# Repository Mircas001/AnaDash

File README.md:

# AnaDash - Resource monitor + macropad 
**THIS IS WIP! NOT TESTED YET!**

This is an resource monitor for your PC, also featuring an macropad, inspired by Alex Bailey's system monitor and Hack Club's hackpad program! It allows you to take a quick glance and see your system information, while keeping the screen free for anything you do!
This was made after watching , I've been wanting to make it for 2 years now! I also added an hackpad after seeing the very helpful 

## Features:
- 4x Analog Gauges showing CPU usage, CPU temperature, RAM usage and Swap usage, driven by an MCP4728 chip!
- 8x Cherry MX keys for any macro your heart wishes!
- An LCD display that can show time, notifications and current song!
- An rotary encoder for changing your volume! Including a switch for mute!

## Case
AnaDash consists of embedded-rust-rp2040 parts, each one split into 
- An case, that supports it and holds it, also houses the raspberry, this part is split in two as it's too big to fit in most printers!
 
- An front plate, that you insert heatset inserts into and then screw the parts in, also split in two!
- An front case, which hides all the PCBs and wiring and gives a nice flush finish, split in two as well!
- An encoder, not split in two, with regular rectangular extruding parts for better grip while also keeping printability!

Since the parts are split in two, you'll have to weld them, use an cheap soldering iron or preferentially an plastic welder for this job, since it can damage soldering tips. I can also help you make an version where both parts are one in case you want to print them as one part.

The design files are available [here](https://cad.onshape.com/documents/ea3d35dc7a38396ad80a61d7/w/835ea08936cef2d122cf7568/e/898c0cf3f941f1983e6f2559)

## PCB
This project was designed in KiCad, it uses a pair of 2 layer PCBs, the PCBs were split because the switches had to be at an angle while the pico had to sit straight.
For this to work, you must connect the following, all of the cables are JST-XH, as it features an locking mechanism.
You must make the following connections: (Pinouts are in left to right, when viewed from abovee!, GND will always be the rounded rectangle!) 
- DisplayConnector (BL, SCK, SDA, CS, RESET, CS, VCC, GND) - connect this to the matching pins on the display.
- LeftKeyConnector (Switch1, Switch2, Switch3, Switch4, GND) - The Input Board has matching connections!
- RightKeyConnector (Switch5, Switch6, Switch7, Switch8, GND) - The Input Board has matching connections!
- EncoderConnector (B, A, Switch, GND) - The Input Board has matching connections!

### Main PCB
This Board features the Pico, the DAC, the outputs for the ammeters, the display connector and the connections to the input board.            

[You can check out the PCB and schematic on KiCanvas!](https://kicanvas.org/?repo=https%3A%2F%2Fgithub.com%2FMircas001%2FAnaDash%2Ftree%2Fmain%2Fhardware%2FmainBoard)                                            

### Input PCB
This PCB has all the keys and the encoder and serves to take inputs, it is angled together with the display and gauges at 45 degrees for ergonomics!                 

[You can check out the PCB and schematic on KiCanvas!](https://kicanvas.org/?repo=https%3A%2F%2Fgithub.com%2FMircas001%2FAnaDash%2Ftree%2Fmain%2Fhardware%2FinputBoard)                                         

## Software
The software has been done entirely in rust, it's memory safe, professional, and has great performance!

Before setting up the software, you'll need to install these programs!
- [rustup](https://rustup.rs) - this is the rust toolchain, and it's the recommended way to compile rust code!
- [probe-rs](https://probe.rs) - **ONLY IF** you are gonna upload via an **debug probe**.
- [picotool](https://github.com/raspberrypi/pico-sdk-tools/releases) - **ONLY IF** you are gonna upload via **USB**.
- [lm-sensors](https://github.com/lm-sensors/lm-sensors) - This provides the sensors the driver can read from! Make sure to set it up before!

It's consisted in 3 parts:
- Firmware: Runs the Pico!
- Driver: Gets the info from your PC!
- Shared library: This is so both firmware and hardware agree with each other!

### Firmware
This firmware supports the Raspberry Pi Pico 1!
There are two ways you can upload it to the pico:

#### Upload via debug probe
For this, you need to connect your debug probe to SWD port!
```bash
git clone https://github.com/Mircas001/AnaDash.git
cd AnaDash/software/firmware
cargo run --release
```

#### Upload via USB
For this, all you need to do is connect the Raspberry Pi Pico to your computer via USB, and run with the usb-deploy feature!
```bash
git clone https://github.com/Mircas001/AnaDash.git
cd AnaDash/software/firmware
cargo run -F usb-deploy --release 
```

### Drivers
This only supports Linux for now! But I can answer questions about the code to help anyone who wants to port it! It works as a systemd service that uses udev rules to start as soon as you plug it in!

#### PKGBUILD method
If you run Arch Linux or any other Arch Based distro, you can use this to install! For now you have to manually install the PKGBUILD, but it'll get uploaded to the AUR once it's done!
**This is the recommended method.**
```bash 
git clone https://github.com/Mircas001/anadash-driver.git
cd anadash-driver
makepkg -si
```

#### Compile it yourself
This is more complicated! But it should work!
1. Make sure you are in the dialout group to get serial perms!
```bash
sudo usermod -aG dialout $USER
```
2. Install all the files!
```bash
git clone https://github.com/Mircas001/AnaDash.git
cd AnaDash/software/driver
cargo build --release
sudo cp target/release/anadash-driver /usr/local/bin
sudo chmod 755 /usr/local/bin/anadash-driver 
sudo cp anadash-driver@.service /etc/systemd/system
sudo cp 99-anadash.rules /etc/udev/rules.d
```
3. Reload everything!
```bash 
sudo systemctl daemon-reload
sudo udevadm control --reload-rules
sudo udevadm trigger
```
It should work as soon as you plug in the device!

You're also always welcome to implement these steps in an package file, so other people with your distro have it easier!

### Troubleshooting the drivers
Since it's an systemd service, you can get the logs like this, replacing ```<serialport>``` with the device's serial port! Usually, it's ttyUSB0.
```bash
systemctl status anadash-driver@<serialport>.service
journalctl -u anadash-driver@<serialport>.service
```

## Assembly  
See [assembly.md](https://github.com/Mircas001/AnaDash/blob/main/ASSEMBLY.md)

## Usage
After installation of drivers, assembly, and flashing, the project SHOULD be plug and play. The macropad uses F13-F21, so to setup the macros, just use plug those keys in whatever software you want!  

## Debugging the device
There is an UART port at the main board for debugging!
Also, there are also some key combinations baked in the firmware:
- You can press the 1st key and the 8th key (the two outhermost keys) to reset the pico!
- You can press the 4th key and the 5th key (the two innermost keys) to go into DFU mode!

## Miscellaneous note
You will need to print the labels for the meters in A4 sticker paper, if you are an manufacturer, you should get it custom printed!                           
The labels are available here: [Labels](https://raw.githubusercontent.com/Mircas001/AnaDash/refs/heads/main/production/meterLabels.svg)

There is an LED header added to the PCB, however, I did not implement the code for it, it is there for future use! You are also free to repurpose it!

## BOM
| Designator                                  | Qty |
| ------------------------------------------- | --- |
| 1.77inch ST7735 Display                     | 1   |
| 85C1 Ammeter 5mA                            | 4   |
| FIXME SCREWS                                | 1   |
| M3 X 4.2 X L4.0 Brass Heatset Insert 100pcs | 1   |
| M2 X 3.2 X L4.0 Brass Heatset Insert 100pcs | 1   |
| Countersunk M3x8mm screw                    | 12  |
| Countersunk M3x20mm screw                   | 4   |
| Panhead M2x8mm screw                        | 4   |
| Panhead M3x8mm screw                        | 4   |
| Cherry MX Compatible Switches 10pcs         | 8   |
| XDA2 1U Keycaps 10pcs                       | 1   |
| EC11 Rotary Encoder 20mm with Switch        | 1   |
| JST-XH Kit                                  | 1   |
| Raspberry Pi Pico                           | 1   |
| MCP4728-E                                   | 1   |
| 10uF Tantalum Capacitor 1206                | 1   |
| 100nF Ceramic Capacitor 1206                | 1   |
| 10KΩ 4x0603 Concave Resistor Network        | 1   |
| 665Ω Resistor                               | 4   |
| Main Board at JLCPCB  (PCBA)                | 1   | 
| Input board at JLCPCB                       | 1   |
| 3D Printed parts                            | 7   | 

Details, such as aliexpress links, LCSC part numbers and cost (as of June 2026) are available here: [BOM](https://github.com/Mircas001/AnaDash/blob/main/production/BOM.csv)

It is strongly recommended

You can also get the JLCPCB BOM for the main board (in case you want to get PCBA) here: [BOM](https://github.com/Mircas001/AnaDash/blob/main/production/mainBoard/jlcpcb_bom.csv)

However, if you do get PCBA, it's recommended to only request the soldering of SMD components, as it's cheaper this way! Also, the 665ohm resistors need to be manually filled in, apparently they're so new there's not even a footprint for it! But I believe this issue will go away with time.         

The input board does not feature an JLCPCB BOM for PCBA because they do not have the parts for it! However, I have left the netlist and positions there in case you have an pick and place machine, but official support for assembling it this way is NOT provided! It's recommended to hand solder instead! Only THD components are used there.

## Software used:
This project was designed in:
- [KiCad for the PCBs!](https://www.kicad.org)
- [Visual Studio Code for the software!](https://code.visualstudio.com/)
- [Onshape for the 3D design!](https://onshape.com/)

## TODO List:
- [X] Design the main PCB 
- [X] Design the input PCB
- [X] Design the meters
- [X] Make the drivers
- [X] Make the driver into an actual driver
- [X] Make the firmware
- [ ] Make the Case

## Credits
- [Lex Bailey, for giving me the inspiration to start this project a few years ago, and for help with the meter labels](https://www.youtube.com/watch?v=4J-DTbZlJ5I)
- [Hack Club Macondo program, for the funding](https://macondo.hackclub.com/)
- [OrpheusPad, for serving as reference as to how should the git repo and README look like](https://github.com/qcoral/orpheuspad/tree/main)
- [HackPad program, which, despite not participating in it, guided me through PCB design](https://hackpad.hackclub.com/)
- [CarlKCarlK's clock project which I'm using as inspiration for parts of the codecode](https://github.com/CarlKCarlK/clock)
- [Siliconwit's guide on embassy-usb](https://siliconwit.com/education/embedded-rust-rp2040/usb-device-embassy/)

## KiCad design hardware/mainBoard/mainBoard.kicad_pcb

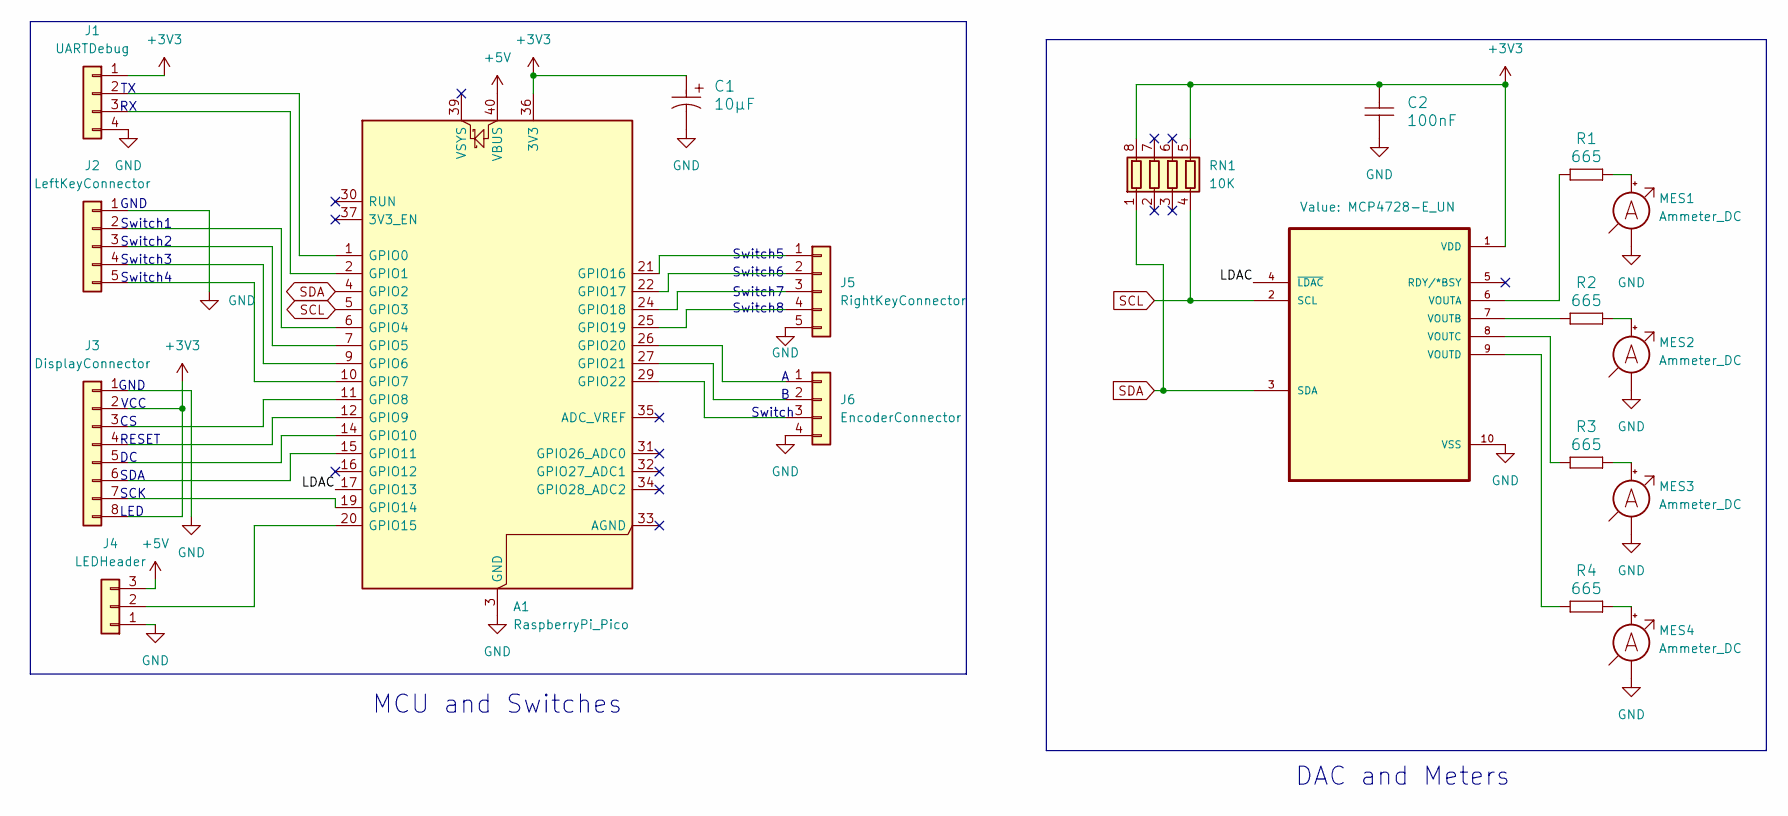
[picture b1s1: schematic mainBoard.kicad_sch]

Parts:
A1: RaspberryPi_Pico; RaspberryPi_Pico_Common_Unspecified; LCSC Part # C42924268
C1: 10µF; CP_EIA-3528-15_AVX-H_HandSolder; LCSC Part # C7171
C2: 100nF; C_1206_3216Metric_Pad1.33x1.80mm_HandSolder; LCSC Part # C24497
J1: UARTDebug; JST_XH_B4B-XH-A_1x04_P2.50mm_Vertical; LCSC Part # C144395
J2: LeftKeyConnector; JST_XH_B5B-XH-A_1x05_P2.50mm_Vertical; LCSC Part # C157991
J3: DisplayConnector; PinHeader_1x08_P2.54mm_Vertical; LCSC Part # C492407
J4: LEDHeader; JST_XH_B3B-XH-A_1x03_P2.50mm_Vertical; LCSC Part # C144394
J5: RightKeyConnector; JST_XH_B5B-XH-A_1x05_P2.50mm_Vertical; LCSC Part # C157991
J6: EncoderConnector; JST_XH_B4B-XH-A_1x04_P2.50mm_Vertical; LCSC Part # C144395
MES1, MES2, MES3, MES4: Ammeter_DC; JST_XH_B2B-XH-A_1x02_P2.50mm_Vertical; LCSC Part # C158012
R1, R2, R3, R4: 665; R_1206_3216Metric_Pad1.30x1.75mm_HandSolder; LCSC Part # C54532953
RN1: 10K; R_Array_Concave_4x0603; LCSC Part # C29718
U1: MCP4728-E_UN; SOP50P490X110-10N; LCSC Part # C108207

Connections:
+3V3: A1.36 (3V3), C1.1, C2.1, J1.1, J3.2, J3.8, RN1.5 (R4.2), RN1.8 (R1.2), U1.1 (VDD)
+5V: A1.40 (VBUS), J4.3
/LDAC: A1.17 (GPIO13), U1.4 (~LDAC)
GND: A1.3 (GND), A1.8 (GND), A1.13 (GND), A1.18 (GND), A1.23 (GND), A1.28 (GND), A1.38 (GND), C1.2, C2.2, J1.4, J2.1, J3.1, J4.1, J5.5, J6.4, MES1.1 (-), MES2.1 (-), MES3.1 (-), MES4.1 (-), U1.10 (VSS)
unnamed: A1.1 (GPIO0), J1.2
unnamed: A1.2 (GPIO1), J1.3
unnamed: A1.6 (GPIO4), J2.2
unnamed: A1.7 (GPIO5), J2.3
unnamed: A1.9 (GPIO6), J2.4
unnamed: A1.10 (GPIO7), J2.5
unnamed: A1.11 (GPIO8), J3.3
unnamed: A1.12 (GPIO9), J3.4
unnamed: A1.14 (GPIO10), J3.5
unnamed: A1.15 (GPIO11), J3.6
unnamed: A1.19 (GPIO14), J3.7
unnamed: A1.20 (GPIO15), J4.2
unnamed: A1.21 (GPIO16), J5.1
unnamed: A1.22 (GPIO17), J5.2
unnamed: A1.24 (GPIO18), J5.3
unnamed: A1.25 (GPIO19), J5.4
unnamed: A1.26 (GPIO20), J6.1
unnamed: A1.27 (GPIO21), J6.2
unnamed: A1.29 (GPIO22), J6.3
unnamed: MES1.2 (+), R1.2
unnamed: MES2.2 (+), R2.2
unnamed: MES3.2 (+), R3.2
unnamed: MES4.2 (+), R4.2
unnamed: R1.1, U1.6 (VOUTA)
unnamed: R2.1, U1.7 (VOUTB)
unnamed: R3.1, U1.8 (VOUTC)
unnamed: R4.1, U1.9 (VOUTD)
SCL: A1.5 (GPIO3), RN1.4 (R4.1), U1.2 (SCL)
SDA: A1.4 (GPIO2), RN1.1 (R1.1), U1.3 (SDA)

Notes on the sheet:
MCU and Switches
GND
Switch2
SCK
Switch
Switch1
DAC and Meters
Switch5
Switch7
GND
Switch6
Switch3
SDA
RESET
Switch8
Switch4
LED
VCC

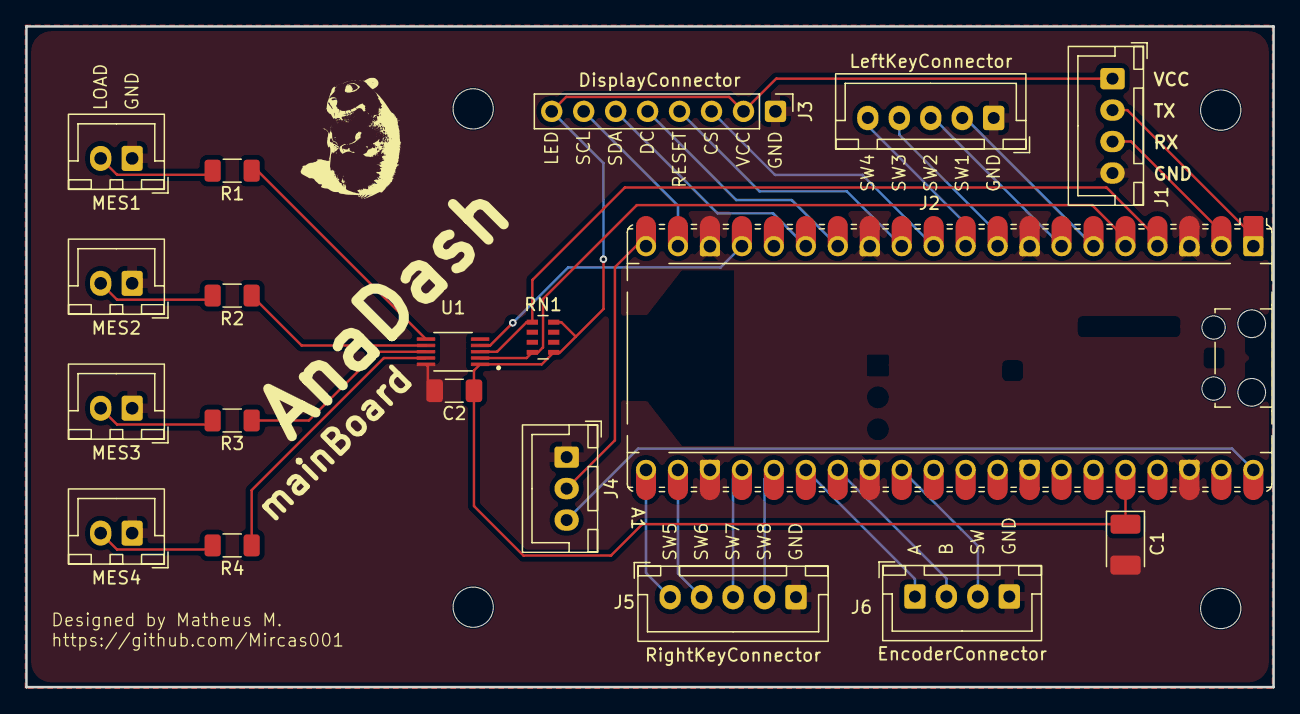
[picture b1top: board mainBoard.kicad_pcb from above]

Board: 2 copper layers, 99.1 x 52.5 mm, 19 parts (0 on the bottom side), 33 nets.

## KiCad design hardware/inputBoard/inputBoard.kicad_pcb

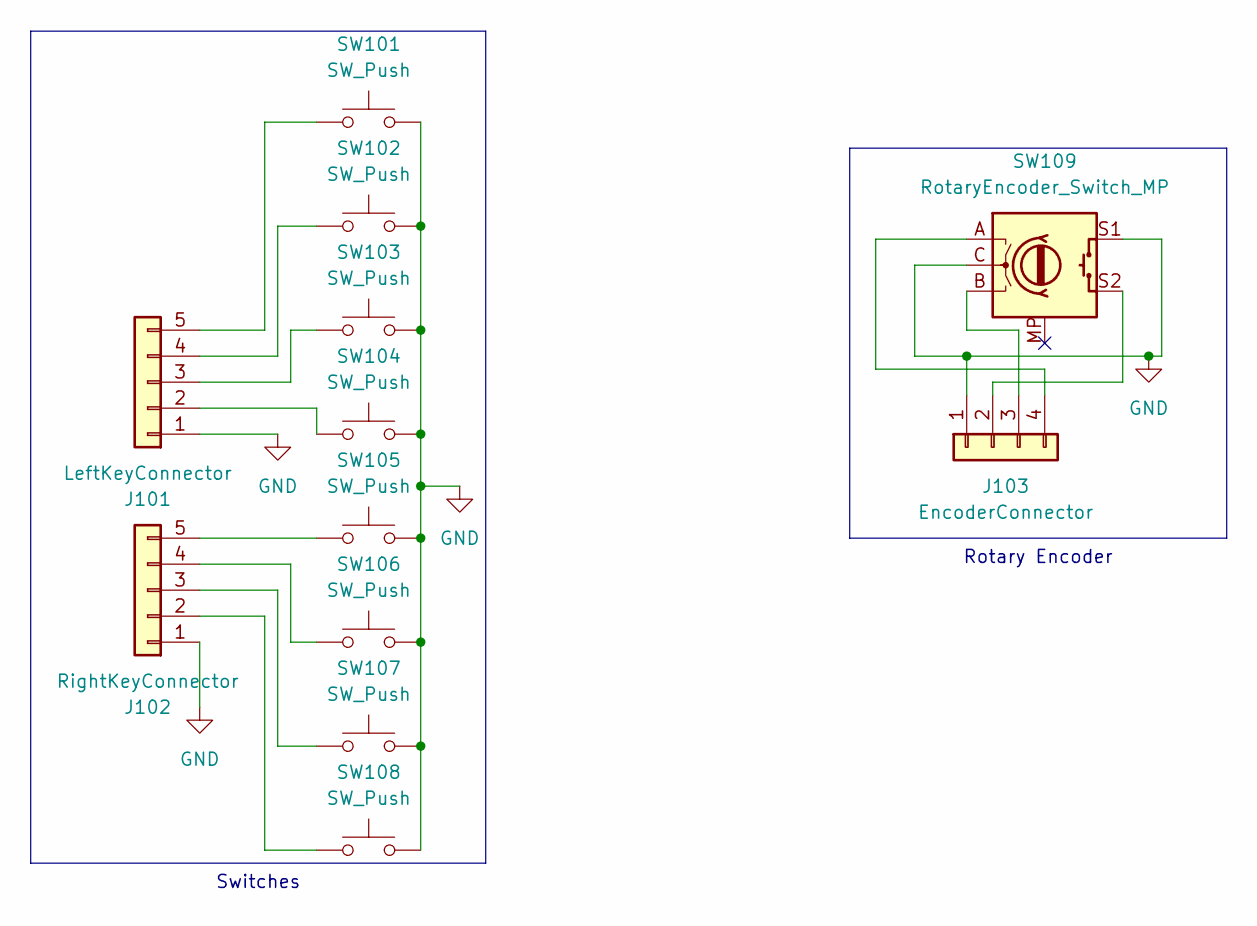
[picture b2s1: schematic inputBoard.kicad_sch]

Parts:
J101: LeftKeyConnector; JST_XH_B5B-XH-A_1x05_P2.50mm_Vertical; LCSC Part # C157991
J102: RightKeyConnector; JST_XH_B5B-XH-A_1x05_P2.50mm_Vertical; LCSC Part # C157991
J103: EncoderConnector; JST_XH_B4B-XH-A_1x04_P2.50mm_Vertical; LCSC Part # C144395
SW101, SW102, SW103, SW104, SW105, SW106, SW107, SW108: SW_Push; SW_Cherry_MX_1.00u_PCB; LCSC Part # N/A
SW109: RotaryEncoder_Switch_MP; RotaryEncoder_Alps_EC11E-Switch_Vertical_H20mm; LCSC Part # C370986

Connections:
GND: J101.1, J102.1, J103.1, SW101.2, SW102.2, SW103.2, SW104.2, SW105.2, SW106.2, SW107.2, SW108.2, SW109.C, SW109.S1
unnamed: J101.2, SW104.1
unnamed: J101.3, SW103.1
unnamed: J101.4, SW102.1
unnamed: J101.5, SW101.1
unnamed: J102.2, SW108.1
unnamed: J102.3, SW107.1
unnamed: J102.4, SW106.1
unnamed: J102.5, SW105.1
unnamed: J103.2, SW109.S2
unnamed: J103.3, SW109.B
unnamed: J103.4, SW109.A

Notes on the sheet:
Switches
Rotary Encoder

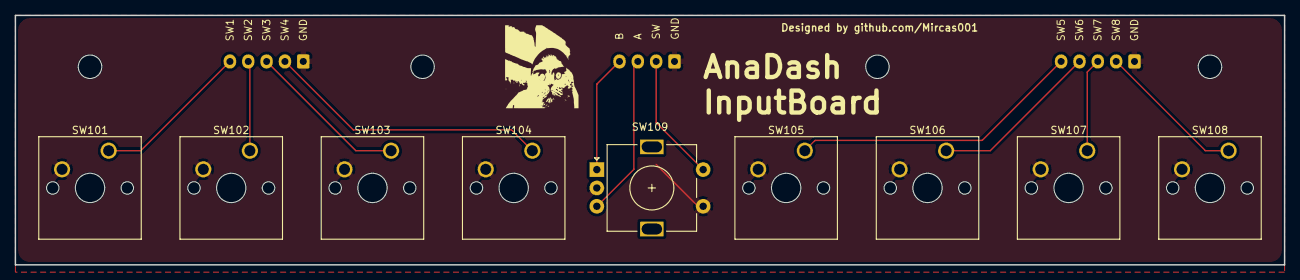
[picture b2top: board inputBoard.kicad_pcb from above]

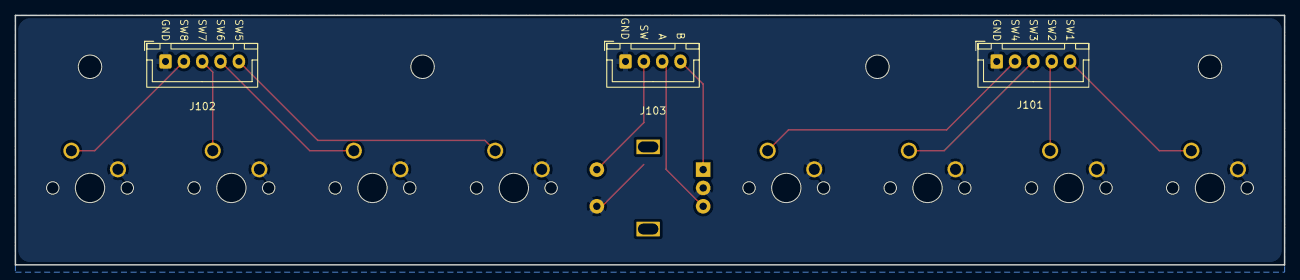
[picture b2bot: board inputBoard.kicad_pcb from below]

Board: 2 copper layers, 173.0 x 34.0 mm, 12 parts (3 on the bottom side), 12 nets.

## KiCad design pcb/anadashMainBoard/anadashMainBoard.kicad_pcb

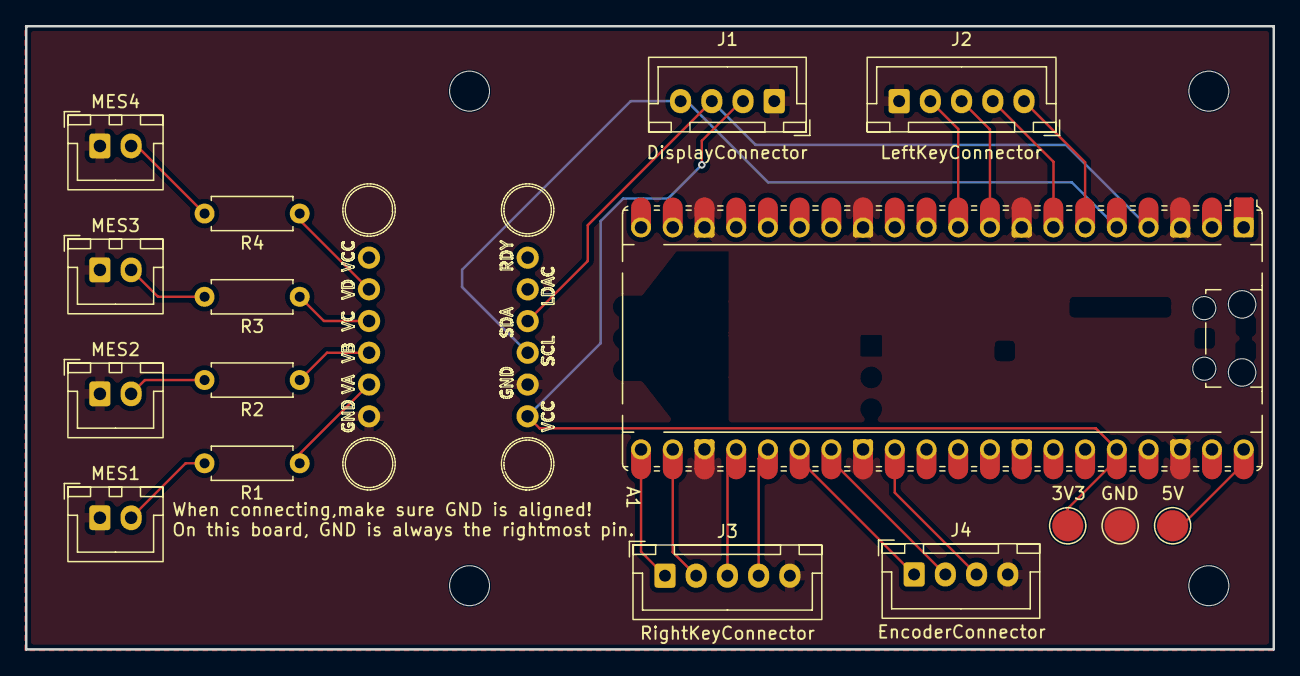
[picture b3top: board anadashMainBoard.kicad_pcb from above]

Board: 2 copper layers, 99.9 x 49.9 mm, 17 parts (0 on the bottom side), 24 nets.

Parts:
A1: RaspberryPi_Pico; RaspberryPi_Pico_Common_Unspecified
J1: DisplayConnector; JST_XH_B4B-XH-A_1x04_P2.50mm_Vertical
J2: LeftKeyConnector; JST_XH_B5B-XH-A_1x05_P2.50mm_Vertical
J3: RightKeyConnector; JST_XH_B5B-XH-A_1x05_P2.50mm_Vertical
J4: EncoderConnector; JST_XH_B4B-XH-A_1x04_P2.50mm_Vertical
MES1, MES2, MES3, MES4: Ammeter_DC; JST_XH_B2B-XH-A_1x02_P2.50mm_Vertical
R1, R2, R3, R4: 680; R_Axial_DIN0207_L6.3mm_D2.5mm_P7.62mm_Horizontal
TP1, TP2, TP3: TestPoint; TestPoint_Pad_D2.5mm
U1: Adafruit_MCP4728

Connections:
+3V3: A1.36 (3V3), J1.2, TP3.1 (1_1), U1.7 (VCC)
+5V: A1.40 (VBUS), TP1.1 (1_1)
GND: A1.3 (GND), A1.8 (GND), A1.13 (GND), A1.18 (GND), A1.23 (GND), A1.28 (GND), A1.38 (GND), J1.1, J2.5, J3.5, J4.4, MES1.1 (-), MES2.1 (-), MES3.1 (-), MES4.1 (-), TP2.1 (1_1), U1.1 (GND), U1.8 (GND)
unnamed: A1.6 (GPIO4), J2.1
unnamed: A1.7 (GPIO5), J2.2
unnamed: A1.9 (GPIO6), J2.3
unnamed: A1.10 (GPIO7), J2.4
unnamed: A1.21 (GPIO16), J3.1
unnamed: A1.22 (GPIO17), J3.2
unnamed: A1.24 (GPIO18), J3.3
unnamed: A1.25 (GPIO19), J3.4
unnamed: A1.26 (GPIO20), J4.1
unnamed: A1.27 (GPIO21), J4.2
unnamed: A1.29 (GPIO22), J4.3
unnamed: MES1.2 (+), R1.2
unnamed: MES2.2 (+), R2.2
unnamed: MES3.2 (+), R3.2
unnamed: MES4.2 (+), R4.2
unnamed: R1.1, U1.2 (VA)
unnamed: R2.1, U1.3 (VB)
unnamed: R3.1, U1.4 (VC)
unnamed: R4.1, U1.5 (VD)
SCL: A1.5 (GPIO3), J1.4, U1.9 (SCL)
SDA: A1.4 (GPIO2), J1.3, U1.10 (SDA)

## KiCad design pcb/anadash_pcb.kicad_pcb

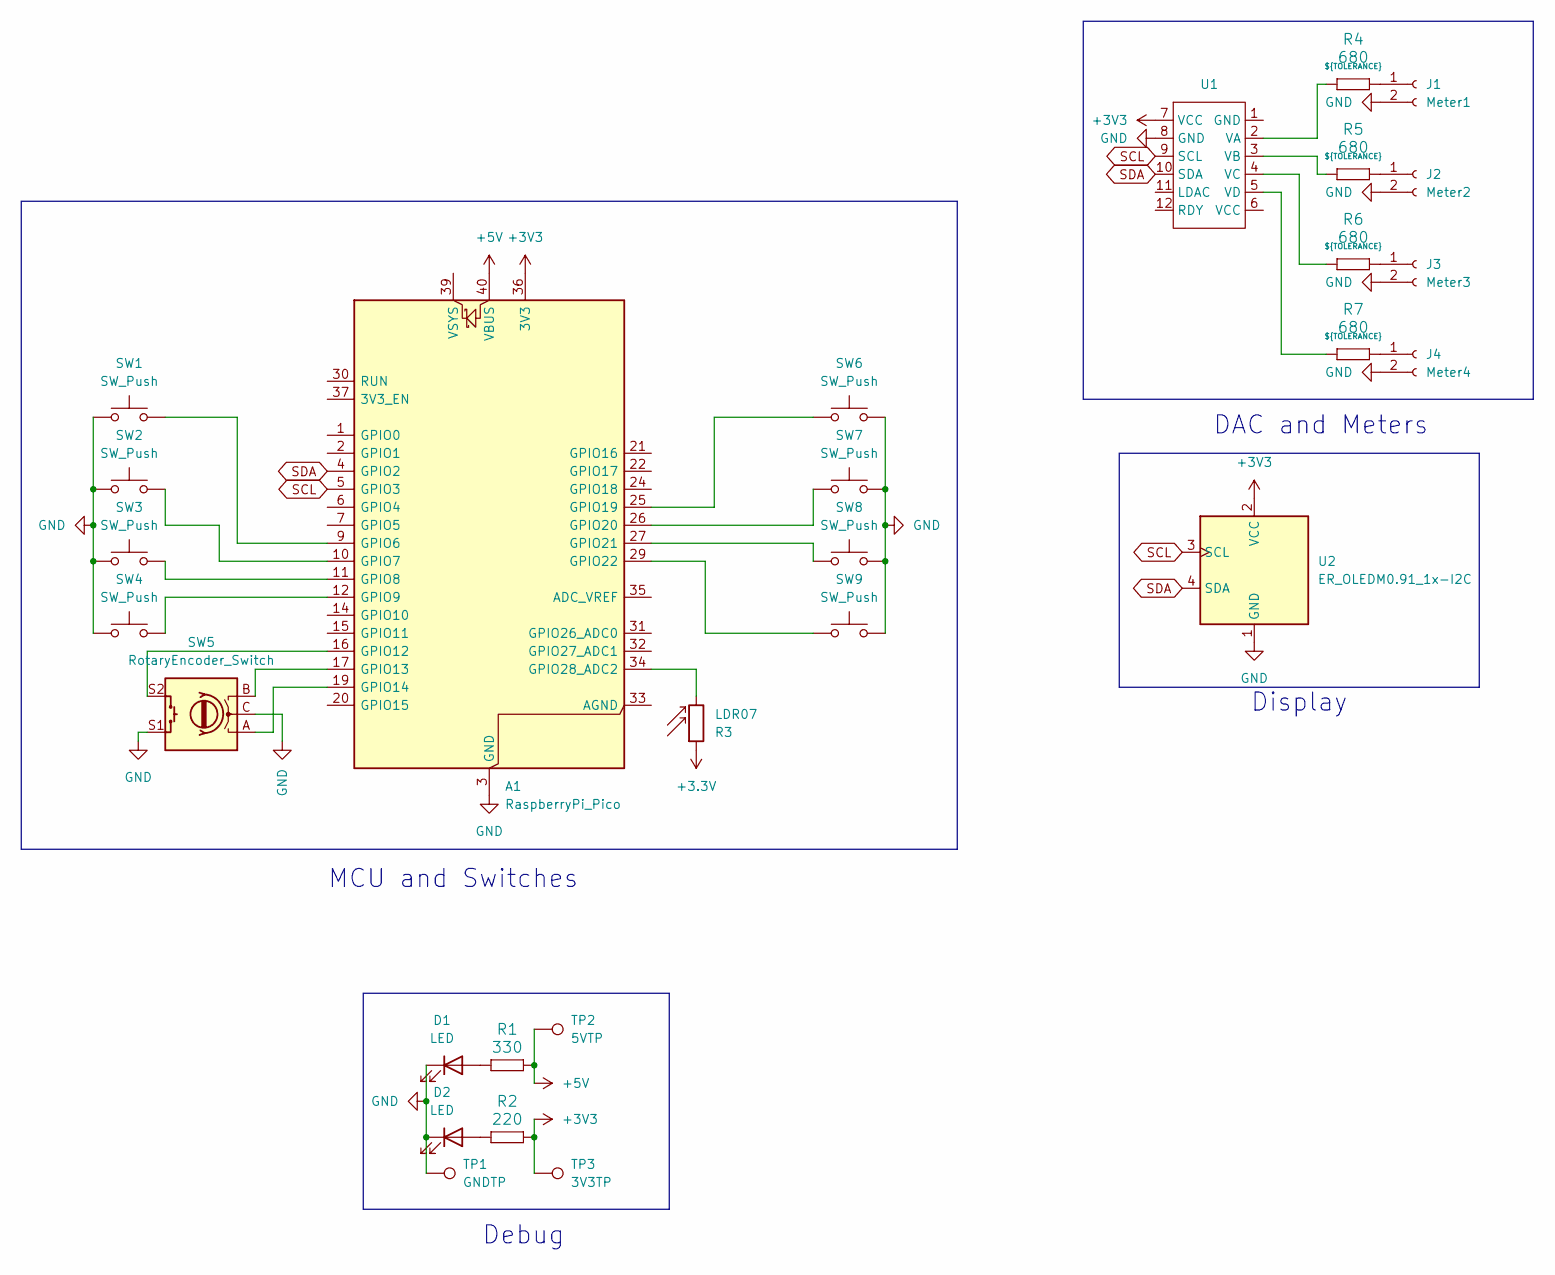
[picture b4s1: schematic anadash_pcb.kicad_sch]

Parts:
A1: RaspberryPi_Pico; RaspberryPi_Pico_Common_Unspecified
D1, D2: LED; LED_D5.0mm
J1: Meter1; JST_XH_B2B-XH-A_1x02_P2.50mm_Vertical
J2: Meter2; JST_XH_B2B-XH-A_1x02_P2.50mm_Vertical
J3: Meter3; JST_XH_B2B-XH-A_1x02_P2.50mm_Vertical
J4: Meter4; JST_XH_B2B-XH-A_1x02_P2.50mm_Vertical
R1: 330; R_Axial_DIN0207_L6.3mm_D2.5mm_P7.62mm_Horizontal
R2: 220; R_Axial_DIN0207_L6.3mm_D2.5mm_P7.62mm_Horizontal
R3: LDR07; R_LDR_5.1x4.3mm_P3.4mm_Vertical
R4, R5, R6, R7: 680; R_Axial_DIN0207_L6.3mm_D2.5mm_P7.62mm_Horizontal; Tolerance ${TOLERANCE}
SW1, SW2, SW3, SW4, SW6, SW7, SW8, SW9: SW_Push; SW_Cherry_MX_1.00u_PCB
SW5: RotaryEncoder_Switch; RotaryEncoder_Alps_EC11E-Switch_Vertical_H20mm
TP1: GNDTP; TestPoint_Pad_D2.0mm
TP2: 5VTP; TestPoint_Pad_D2.0mm
TP3: 3V3TP; TestPoint_Pad_D2.0mm
U1: Adafruit_MCP4728
U2: ER_OLEDM0.91_1x-I2C; Adafruit_SSD1306

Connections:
+3.3V: R3.1
+3V3: A1.36 (3V3), R2.2, TP3.1 (1_1), U1.7 (VCC), U2.2 (VCC)
+5V: A1.40 (VBUS), R1.2, TP2.1 (1_1)
GND: A1.3 (GND), A1.8 (GND), A1.13 (GND), A1.18 (GND), A1.23 (GND), A1.28 (GND), A1.38 (GND), D1.1 (K), D2.1 (K), J1.2, J2.2, J3.2, J4.2, SW1.1, SW2.1, SW3.1, SW4.1, SW5.C, SW5.S1, SW6.1, SW7.1, SW8.1, SW9.1, TP1.1 (1_1), U1.8 (GND), U2.1 (GND)
unnamed: A1.9 (GPIO6), SW1.2
unnamed: A1.10 (GPIO7), SW2.2
unnamed: A1.11 (GPIO8), SW3.2
unnamed: A1.12 (GPIO9), SW4.2
unnamed: A1.16 (GPIO12), SW5.S2
unnamed: A1.17 (GPIO13), SW5.B
unnamed: A1.19 (GPIO14), SW5.A
unnamed: A1.25 (GPIO19), SW6.2
unnamed: A1.26 (GPIO20), SW7.2
unnamed: A1.27 (GPIO21), SW8.2
unnamed: A1.29 (GPIO22), SW9.2
unnamed: A1.34 (GPIO28_ADC2), R3.2
unnamed: D1.2 (A), R1.1
unnamed: D2.2 (A), R2.1
unnamed: J1.1, R4.2
unnamed: J2.1, R5.2
unnamed: J3.1, R6.2
unnamed: J4.1, R7.2
unnamed: R4.1, U1.2 (VA)
unnamed: R5.1, U1.3 (VB)
unnamed: R6.1, U1.4 (VC)
unnamed: R7.1, U1.5 (VD)
SCL: A1.5 (GPIO3), U1.9 (SCL), U2.3 (SCL)
SDA: A1.4 (GPIO2), U1.10 (SDA), U2.4 (SDA)

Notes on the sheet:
MCU and Switches
DAC and Meters
Debug
Display

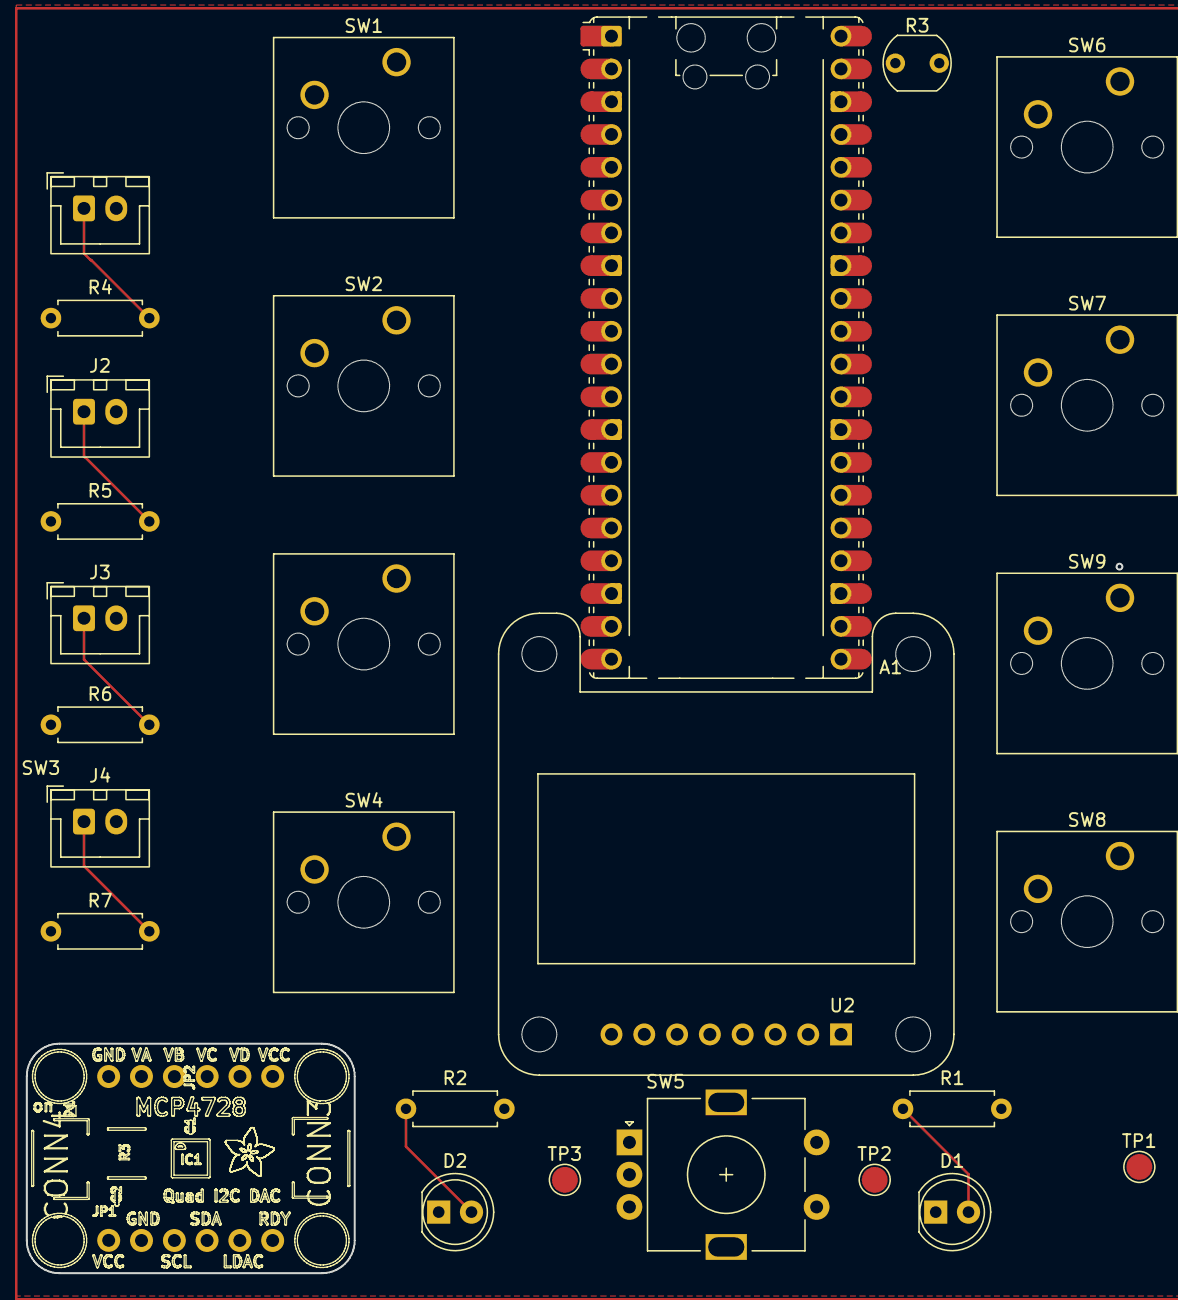
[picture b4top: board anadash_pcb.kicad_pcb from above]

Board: 2 copper layers, 28 parts (0 on the bottom side), 27 nets.

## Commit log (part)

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2026-06-25 Add project title and description to README
2026-06-27 Drawed up the DAC n meters
2026-06-28 Finish up the schematic
2026-06-28 esp32 switch :d
2026-06-28 Something something
2026-06-29 Revert "Something something"
    This reverts commit 5c7b6453f34c5b8c75ef92b91872553d5c75635f.
2026-06-29 Revert "esp32 switch :d"
    This reverts commit a7c39a4a50a5a8529a2412f65cccd0cacde0d017.
2026-06-30 Added test pads, change the switches's wiring, added an encoder
